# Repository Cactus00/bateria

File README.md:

# bateria
baterias. Aqui la placa con salidas a jack hembra, y OPZ.

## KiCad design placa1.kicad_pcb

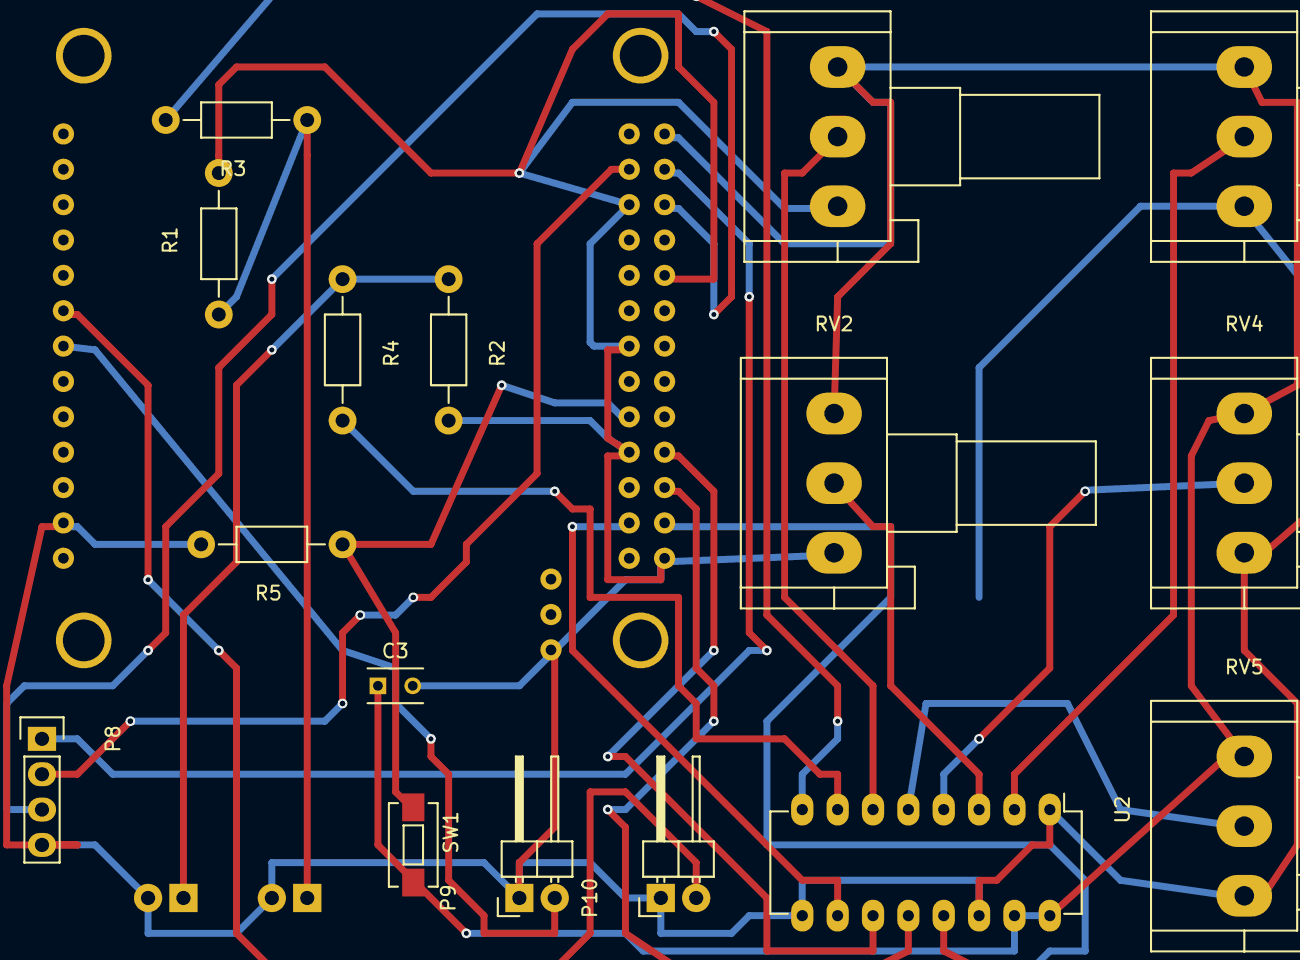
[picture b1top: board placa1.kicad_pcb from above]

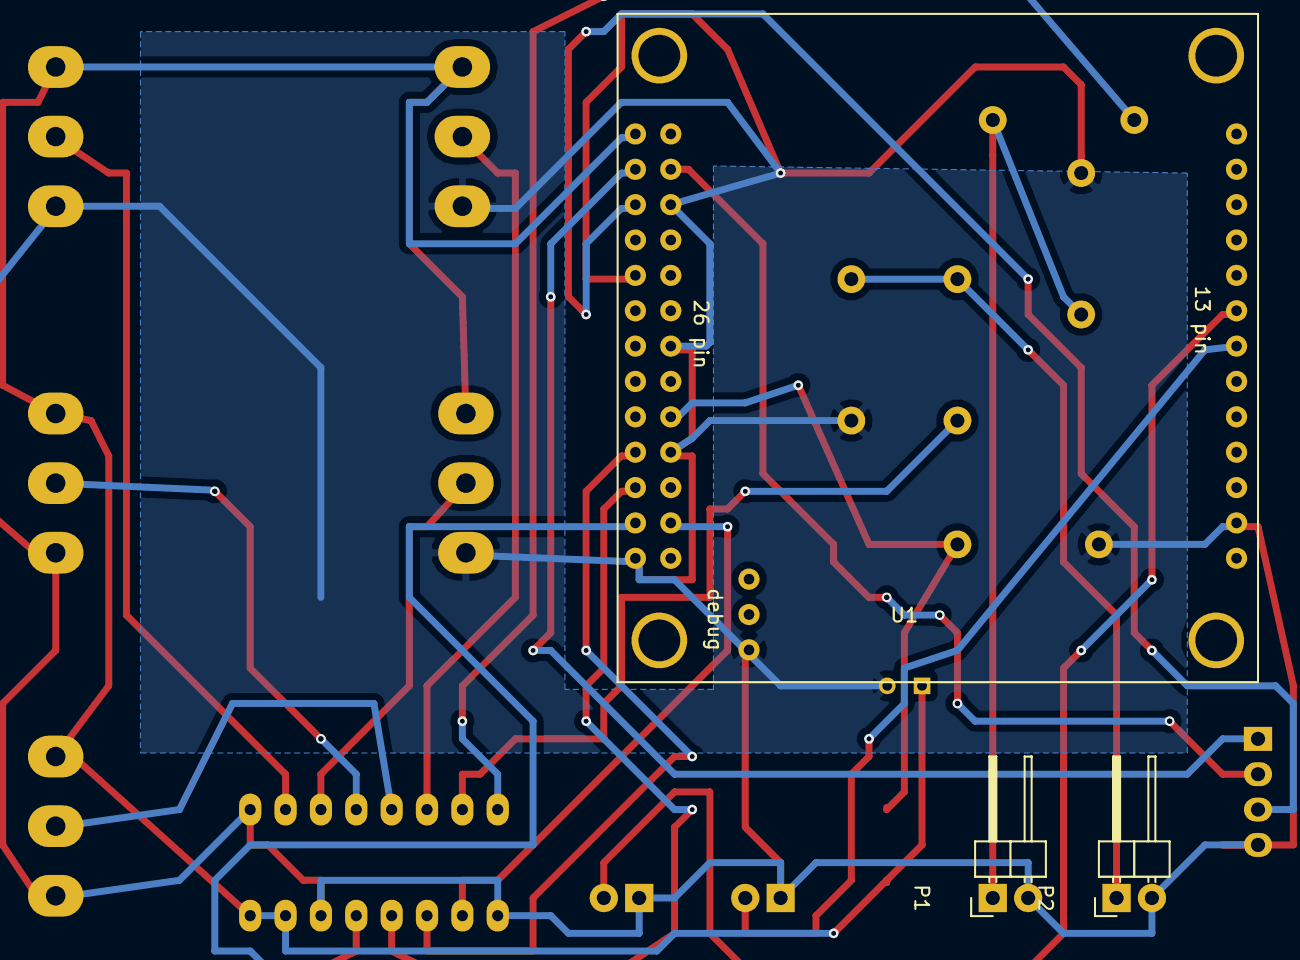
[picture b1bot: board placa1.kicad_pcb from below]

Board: 2 copper layers, 19 parts (3 on the bottom side), 21 nets.

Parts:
C3: C; C_Rect_L4_W2.5_P2.5
P1, P2, P9, P10: CONN_01X02; Pin_Header_Angled_1x02
P8: CONN_01X04; Socket_Strip_Straight_1x04
R1, R2, R3, R4, R5: R; Resistor_Horizontal_RM10mm
RV1, RV2, RV3, RV4, RV5: POT; Potentiometer_Alps-RK16-single_largePads
SW1: SW_PUSH; SW_SPST_EVQPE1
U1: orange_pi_zero; orangepi-zero
U2: MCP3008; DIP-16_W7.62mm_LongPads

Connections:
+3V3: C3.1, RV1.1, RV2.1, RV3.1, RV4.1, RV5.1, SW1.2, U1.101, U2.15, U2.16
Earth: C3.2, P1.2, P2.2, P8.4, P9.1, P10.1, R1.2, R2.2, R5.2, RV1.3, RV2.3, RV3.3, RV4.3, RV5.3, U1.2, U1.106, U1.109, U1.114, U1.120, U1.125, U1.201, U2.1, U2.9, U2.14
unnamed: P1.1, R1.1, R3.1
unnamed: P2.1, R2.1, R4.1
unnamed: P8.1, U1.103
unnamed: P8.2, U1.104
unnamed: P8.3, U1.105
unnamed: P9.2, U1.7
unnamed: P10.2, U1.8
unnamed: R3.2, U2.8
unnamed: R4.2, U2.7
unnamed: R5.1, SW1.1, U1.118
unnamed: RV1.2, U2.6
unnamed: RV2.2, U2.3
unnamed: RV3.2, U2.2
unnamed: RV4.2, U2.4
unnamed: RV5.2, U2.5
unnamed: U1.119, U2.11
unnamed: U1.121, U2.12
unnamed: U1.123, U2.13
unnamed: U1.124, U2.10

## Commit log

2018-01-02 Placa bateria.
    Se agrega la placa de la bateria que se está realizando, y el proyecto para
    Kicad.
